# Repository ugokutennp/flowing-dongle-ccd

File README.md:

# FlowingDongleCCD
DIY Multiple Connection Watchman Dongle for SteamVR

FlowingDongle is a very simple dongle for SteamVR that can connect four devices simultaneously with a built-in nrf52840 module and a USB hub.
## Hardware
Includes PCB data created in kicad6 and 3D model data of the case.
The main components are made of the following.
|| components |
|--|--|
| USB 2.0 Hub Controller |FE1.1s  |
|nrf52840 module| MS88SF2 |

BOM can be viewed [here](https://htmlpreview.github.io/?https://github.com/ugokutennp/FlowingDongleCCD/blob/main/Hardware/PCB/flowing_dongle/flowing_dongle_bom.html).
The PCB design and schematic is minimal and not perfect, although stable operation has been confirmed.

[schematic](https://github.com/ugokutennp/FlowingDongleCCD/blob/main/images/flowing_dongle_schematic.pdf),
[pcb_design](https://github.com/ugokutennp/FlowingDongleCCD/blob/main/images/flowing_dongle_pcb.jpg)

## Firmware
By writing the four hex files via SWD using a device such as Jlink, it can be used immediately as a Watchman Dongle.
Firmware comes from the following locations.
|   |  name |  place |
|---|---|---|
| Bootloader  |  nrf52840_xxaa_debug.hex |  nRF5_SDK_17.1.0_ddde560\examples\dfu\open_bootloader\pca10056_usb_debug\armgcc |
|  MBR |  mbr_nrf52_2.4.1_mbr.hex | nRF5_SDK_17.1.0_ddde560\components\softdevice\mbr\hex  | 
|  SoftDevice |  s140_nrf52_6.1.1_softdevice.bin |  C:\Program Files (x86)\Steam\steamapps\common\SteamVR\drivers\indexhmd\resources\firmware\radio\gd_1558748372_dfu | 
| Application  |  temp_app_stamped.bin |  C:\Program Files (x86)\Steam\steamapps\common\SteamVR\drivers\indexhmd\resources\firmware\radio\gd_1558748372_dfu | 

## Bootloader build
Install [Make for Windows](https://gnuwin32.sourceforge.net/packages/make.htm) and Arm Embedded Toolchain ([gcc-arm-none-eabi-9-2020-q2-update-win32.exe](https://developer.arm.com/downloads/-/gnu-rm)) and build with the following command.

    cd Desktop\nRF5_SDK_17.1.0_ddde560\examples\dfu\open_bootloader\pca10056_usb_debug\armgcc
    make

## IndexHMD firmware optimization
Open temp_app_stamped.bin with a hex editor and edit the following items.
| adress  |  before |  after | effect |
|---|---|---|---|
| 0x1839D  |  B1|B9 |disable index audio device |
|  0x162E0 |  Valve VR Radio | any string you like| rename USB device|

## Firmware conversion (bin to hex)
Convert firmware using [srec_cat_exe](https://sourceforge.net/projects/srecord/files/srecord-win32/).

    cd C:\Users\marim\Desktop\Dongle\gd_1558748372_dfu
    srec_cat.exe s140_nrf52_6.1.1_softdevice.bin -Binary -offset 0x1000 -o s140_nrf52_6.1.1_softdevice.hex -Intel
    srec_cat.exe temp_app_stamped.bin -Binary -offset 0x26000 -o temp_app_stamped.hex -Intel
## License
The license applies to hardware data only.

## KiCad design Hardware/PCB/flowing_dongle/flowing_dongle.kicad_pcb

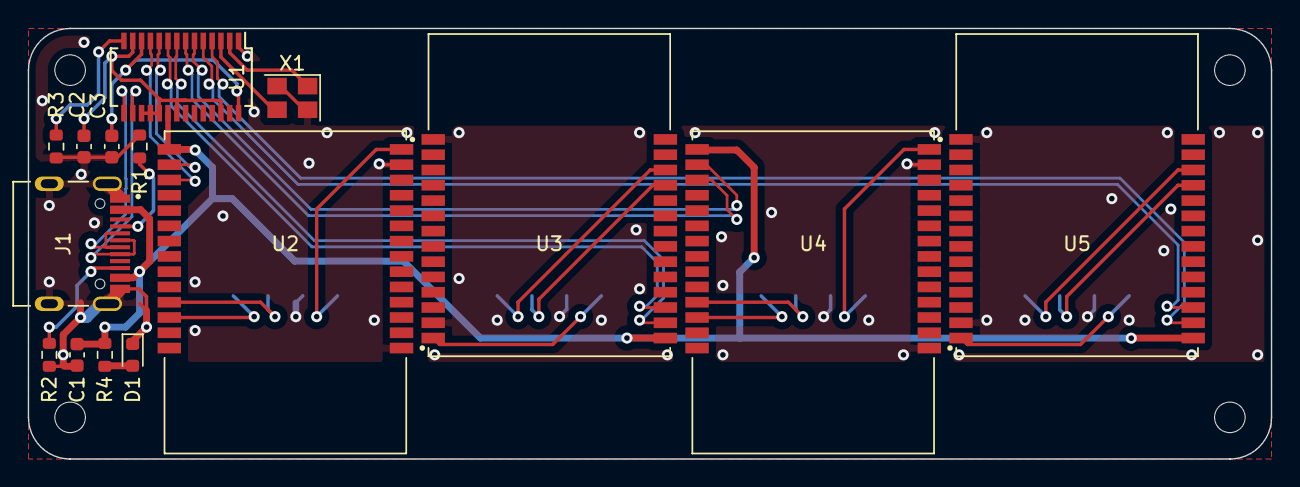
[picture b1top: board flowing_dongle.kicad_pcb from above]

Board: 2 copper layers, 89.5 x 31.0 mm, 15 parts (0 on the bottom side), 20 nets.

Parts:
C1, C2, C3: 10uF; C_0603_1608Metric
D1: LED; LED_0603_1608Metric
J1: TYPE-C-31-M-12; HRO_TYPE-C-31-M-12
R1, R2: 5.1k; R_0603_1608Metric
R3: 2.7kΩ(+-1%); R_0603_1608Metric
R4: R; R_0603_1608Metric
U1: FE1.1s; SSOP-28_3.9x9.9mm_P0.635mm
U2, U3, U4, U5: MS88SF2; XCVR_MS88SF2
X1: 12MHz; Crystal_SMD_3225-4Pin_3.2x2.5mm

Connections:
1DN: U1.10 (DM1), U2.16 (D-)
1DP: U1.11 (DP1), U2.17 (D+)
2DN: U1.8 (DM2), U3.16 (D-)
2DP: U1.9 (DP2), U3.17 (D+)
3DN: U1.6 (DM3), U4.16 (D-)
3DP: U1.7 (DP3), U4.17 (D+)
4DN: U1.4 (DM4), U5.16 (D-)
4DP: U1.5 (DP4), U5.17 (D+)
+1V8: C3.1, U1.12 (VD18_O), U1.28 (VD18)
+3.3V: C2.1, U1.13 (VD33), U1.17 (~XRSTJ), U1.18 (VBUSM), U1.19 (BUSJ), U1.21 (VD33_O), U1.26 (OVCJ)
DN: J1.A7 (DN1), J1.B7 (DN2), U1.15 (DMU)
DP: J1.A6 (DP1), J1.B6 (DP2), U1.16 (DPU)
GND: C1.2, C2.2, C3.2, D1.1 (K), J1.A1B12 (GND), J1.B1A12 (GND), J1.S1 (SHIELD), J1.S2 (SHIELD), J1.S3 (SHIELD), J1.S4 (SHIELD), R1.2, R2.1, R3.1, U1.1 (VSS), U2.1 (GND), U2.13 (GND), U3.1 (GND), U3.13 (GND), U4.1 (GND), U4.13 (GND), U5.1 (GND), U5.13 (GND), X1.2, X1.4
unnamed: D1.2 (A), R4.2
unnamed: J1.A5 (CC1), R1.1
unnamed: J1.B5 (CC2), R2.2
unnamed: R3.2, U1.14 (REXT)
unnamed: U1.2 (XOUT), X1.1
unnamed: U1.3 (XIN), X1.3
VBUS: C1.1, J1.A4B9 (VBUS), J1.B4A9 (VBUS), R4.1, U1.20 (VDD5), U2.15 (VDDH), U3.15 (VDDH), U4.15 (VDDH), U5.15 (VDDH)

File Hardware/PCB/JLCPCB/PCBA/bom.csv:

Designator,Footprint,Quantity,Value,LCSC Part #
"C1, C2, C3",0603,3,10uF,
D1,0603,1,LED,
J1,HRO_TYPE-C-31-M-12,1,TYPE-C-31-M-12,
"R1, R2",0603,2,5.1k,
R3,0603,1,2.7kΩ(+-1%),
R4,0603,1,R,
U1,SSOP-28_3.9x9.9mm_P0.635mm,1,FE1.1s,
"U2, U3, U4, U5",XCVR_MS88SF2,4,MS88SF2,
X1,Crystal_SMD_3225-4Pin_3.2x2.5mm,1,12MHz,
